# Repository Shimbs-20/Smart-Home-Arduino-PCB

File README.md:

# Smart Home IoT Shield for Arduino (220V Control) 🏠

This project is a custom-designed PCB Shield for Arduino that enables safe control of high-voltage home appliances (220V AC) via a mobile application.

## ⚡ Features
* **Safety First:** Designed with proper **creepage and clearance** slots to isolate 220V AC from the 5V logic.
* **Wireless Control:** Integrated header for ESP8266/HC-05 modules for WiFi/Bluetooth connectivity.
* **Noise Immunity:** Optical isolation (Optocouplers) to prevent relay switching noise from resetting the microcontroller.
* **Power Management:** On-board SMPS / Linear regulator to power the Arduino from 12V.

## 🛠️ Hardware Specs
* **Relays:** 4x 10A 220V SPDT Relays.
* **Isolation:** PC817 Optocouplers.
* **Connectors:** High-current screw terminals for AC loads.

## 📂 Folder Structure
* `hardware/` - Source files (KiCad) and Gerber production files.
* `firmware/` - Arduino code for serial communication with the Mobile App.
* `docs/` - PDF Schematic and BOM (Bill of Materials).

## 👨‍💻 Author
**Youssef S.** - Mechatronics & PCB Design Engineer

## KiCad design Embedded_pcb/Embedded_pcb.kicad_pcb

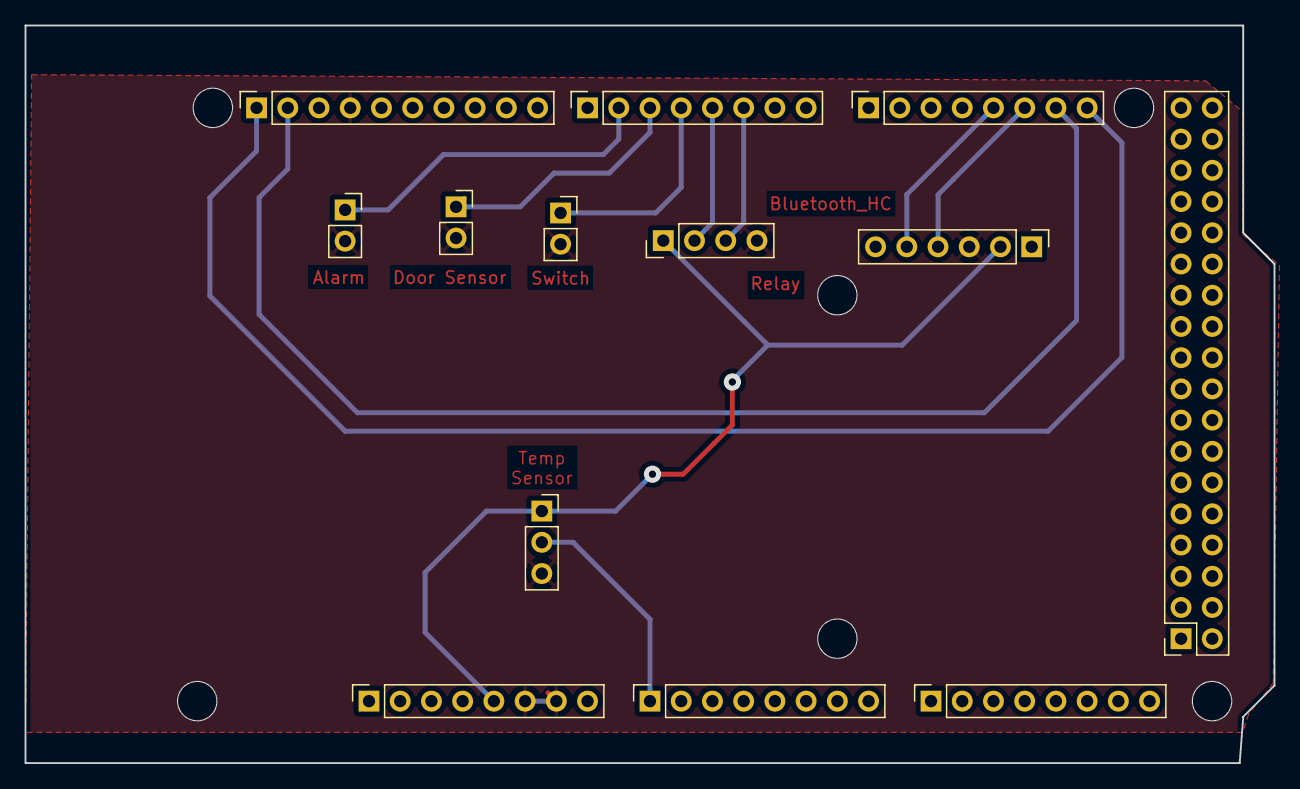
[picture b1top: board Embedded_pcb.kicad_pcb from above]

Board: 2 copper layers, 101.6 x 60.0 mm, 19 parts (0 on the bottom side), 12 nets.

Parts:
J1: Power; PinSocket_1x08_P2.54mm_Vertical
J2: PWM; PinSocket_1x10_P2.54mm_Vertical
J3, J5: Analog; PinSocket_1x08_P2.54mm_Vertical
J4: PWM; PinSocket_1x08_P2.54mm_Vertical
J6: Communication; PinSocket_1x08_P2.54mm_Vertical
J7: Digital; PinSocket_2x18_P2.54mm_Vertical
J8: Bluetooth_HC; PinHeader_1x06_P2.54mm_Vertical
J9: Relay; PinHeader_1x04_P2.54mm_Vertical
J10: Door Sensor; PinSocket_1x02_P2.54mm_Vertical
J11: Switch; PinSocket_1x02_P2.54mm_Vertical
J12: Conn_01x03; PinSocket_1x03_P2.54mm_Vertical
J13: Alarm; PinSocket_1x02_P2.54mm_Vertical
MH1, MH2, MH3, MH4, MH5, MH6: MountingHole_3.2mm

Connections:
+5V: J1.5, J8.2, J9.1, J12.1
/*2: J4.6, J9.3
/*3: J4.5, J9.2
/*4: J4.4, J11.1
/*5: J4.3, J10.1
/*6: J4.2, J13.1
/A0: J3.1, J12.2
/BT_RX: J6.5, J8.5
/BT_TX: J6.6, J8.4
/SCL/21: J2.1, J6.8
/SDA/20: J2.2, J6.7
GND: J1.6, J1.7, J2.4, J8.3, J9.4, J10.2, J11.2, J12.3, J13.2
